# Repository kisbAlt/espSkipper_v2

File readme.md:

<div align="center">
  <picture>
    <source media="(prefers-color-scheme: dark)" srcset="./documentation/logo_dark.png">
    
  </picture>
  <h2 align="center">ESP32 Boat Instrument</h2>
</div>

## ESPSkipper

ESP32 based, open source, low cost boat instrumentation to replace proprietary marine systems.

## Features

- GPS based speed display
- Dynamic multi-function display showing real-time metrics
- Using ST7306 300x400 reflective for good outdoors visibility with custom illumination
- Multi language support
- Configuration through settings page
- Open Echo integration, supports depth readings from the TUSS4470 shield through serial connection
- Rugged 3D printed weather-resistant housing
- Reading water temp thermistors from analog transducers

## Tech Stack

**ESP32:** C++, PlatformIO, Arduino Platform, KiCad  

## Custom PCB

You can find the custom PCB files for KiCad in the hardware folder.

<div align="center" style="display: flex; justify-content: center; align-items: center; gap: 16px; flex-wrap: wrap;">

</div>

### ESP32-S3 pinout:

| Module | Signal | GPIO | Notes |
|---|---|---:|---|
| Display / LIS3DH | LCD_SCLK / SPC | GPIO12 | Shared clock for both devices |
| Display / LIS3DH | LCD_SDI / SDO / MOSI | GPIO11 | Shared data output |
| Display / LIS3DH | SDI / MISO | GPIO13 | Shared data input; ignored for LCD |
| LIS3DH | CS | GPIO10 | Dedicated chip select for device 1 |
| Display (PCB variant) | LCD_RES | GPIO4 | Alternate board mapping |
| Display (PCB variant) | LCD_D/C | GPIO9 | Alternate board mapping |
| Display (PCB variant) | LCD_CS | GPIO5 | Alternate board mapping |
| Display (PCB variant) | LCD_SCLK | GPIO12 | Alternate board mapping |
| Display (PCB variant) | LCD_SDI | GPIO11 | Alternate board mapping |
| LIS3DH (PCB variant) | SDO | GPIO13 | Alternate board mapping |
| LIS3DH (PCB variant) | SDI | GPIO11 | Alternate board mapping |
| LIS3DH (PCB variant) | SPC | GPIO12 | Alternate board mapping |
| LIS3DH (PCB variant) | CS | GPIO10 | Alternate board mapping |
| GNSS (L96-M33) | RX0 | GPIO36 | GPS receiver input |
| GNSS (L96-M33) | TX0 | GPIO37 | GPS receiver output |
| GNSS (L96-M33) | FORCE_ON | GPIO35 | Module power control |
| Serial | TX1 | GPIO6 | Serial port 1 output |
| Serial | RX1 | GPIO7 | Serial port 1 input |
| Serial | TX2 | GPIO15 | Serial port 2 output |
| Serial | RX2 | GPIO16 | Serial port 2 input |
| Buttons | BTN1 | GPIO21 | Front panel button |
| Buttons | BTN2 | GPIO14 | Front panel button |
| Buttons | BTN3 | GPIO3 | Front panel button |
| Buttons | BTN4 | GPIO8 | Front panel button |

## Instrument housing

## PCB Bill of Materials (BOM)

| Ref | Qty | Value | Notes |
|---|---:|---|---|
| U2 | 1 | ESP32-S3-WROOM-1 | Main MCU |
| U1 | 1 | L96-M33 | GNSS module |
| U4 | 1 | LIS3DH | Accelerometer |
| U5 | 1 | - | Micro USB connector |
| U6 | 1 | - | 3.3V regulator |
| BT1 | 1 | 1056 | Battery holder |
| RF1 | 1 | 6GHz | SMA antenna connector |
| FPC1 | 1 | - | Flex cable connector |
| S1, S2 | 2 | FSM8JH | Tactile switches |
| J1 | 1 | Conn_01x10_Pin | 10-pin header |
| J2, J4 | 2 | Conn_01x04_Pin | 4-pin header |
| J3 | 1 | ARDUINO_IN | Arduino interface header |
| J5, J6 | 2 | Conn_01x02_Pin | 2-pin header |
| J7 | 1 | INT1_INT2 | Interrupt header |
| D2 | 1 | SMAJ5 | TVS diode |
| D1 | 1 | - | Schottky diode |
| D6 | 1 | 3V3PWR | 3.3V power LED |
| Q1, Q2 | 2 | - | S8050 transistor pair |
| L1 | 1 | 47 nH | Inductor |
| C1, C2, C3, C4, C16, C18, C20 | 7 | 10uF | Decoupling capacitor |
| C6, C22, C23, C24, C25, C26, C27, C28, C29 | 9 | 1uF | Filter / bulk capacitor |
| C5, C7, C8, C9, C10, C11, C17, C19, C21 | 9 | 100nF | Decoupling capacitor |
| R1, R7, R8, R9, R18, R19 | 6 | 100Ω | Current / pull-up resistor |
| R10, R11, R12, R13, R16, R17 | 6 | 1kΩ | LED / logic resistor |
| R3, R4, R5, R6, R14 | 5 | 10kΩ | Pull-up / bias resistor |
| R2 | 1 | 10Ω | Series resistor |
| R15 | 1 | 0Ω | Link / jumper resistor |
| TP1 | 1 | RESET | Test point |
| TP2 | 1 | EXTINT0 | Test point |
| TP3 | 1 | JAM_DET | Test point |

## Acknowledgements

 - [Open Echo](https://github.com/Neumi/open_echo)
 - [Osptek 4.2" BWR TFT Driver for ESP32-S3 (ST7306)](https://github.com/CaiZiYuan2019/Osptek-4.2-BWR-TFT-Driver-for-ESP32-S3)

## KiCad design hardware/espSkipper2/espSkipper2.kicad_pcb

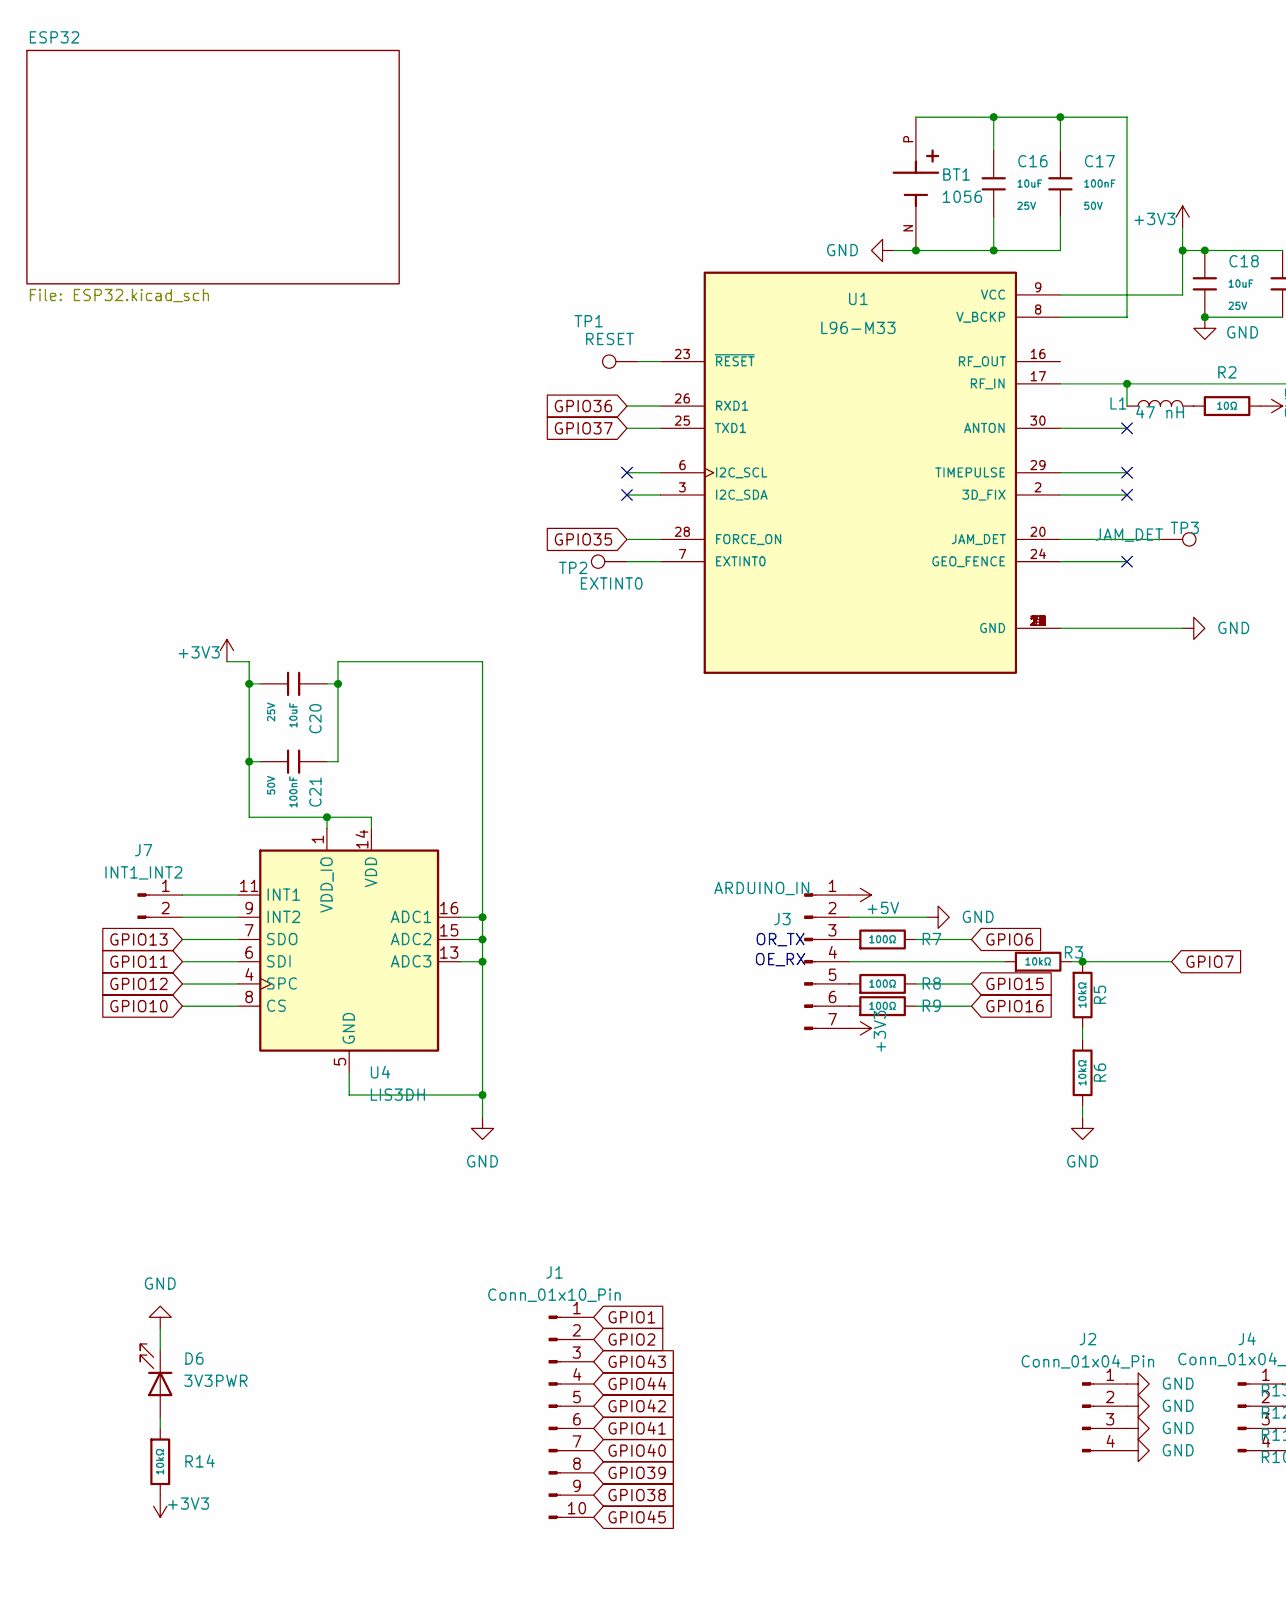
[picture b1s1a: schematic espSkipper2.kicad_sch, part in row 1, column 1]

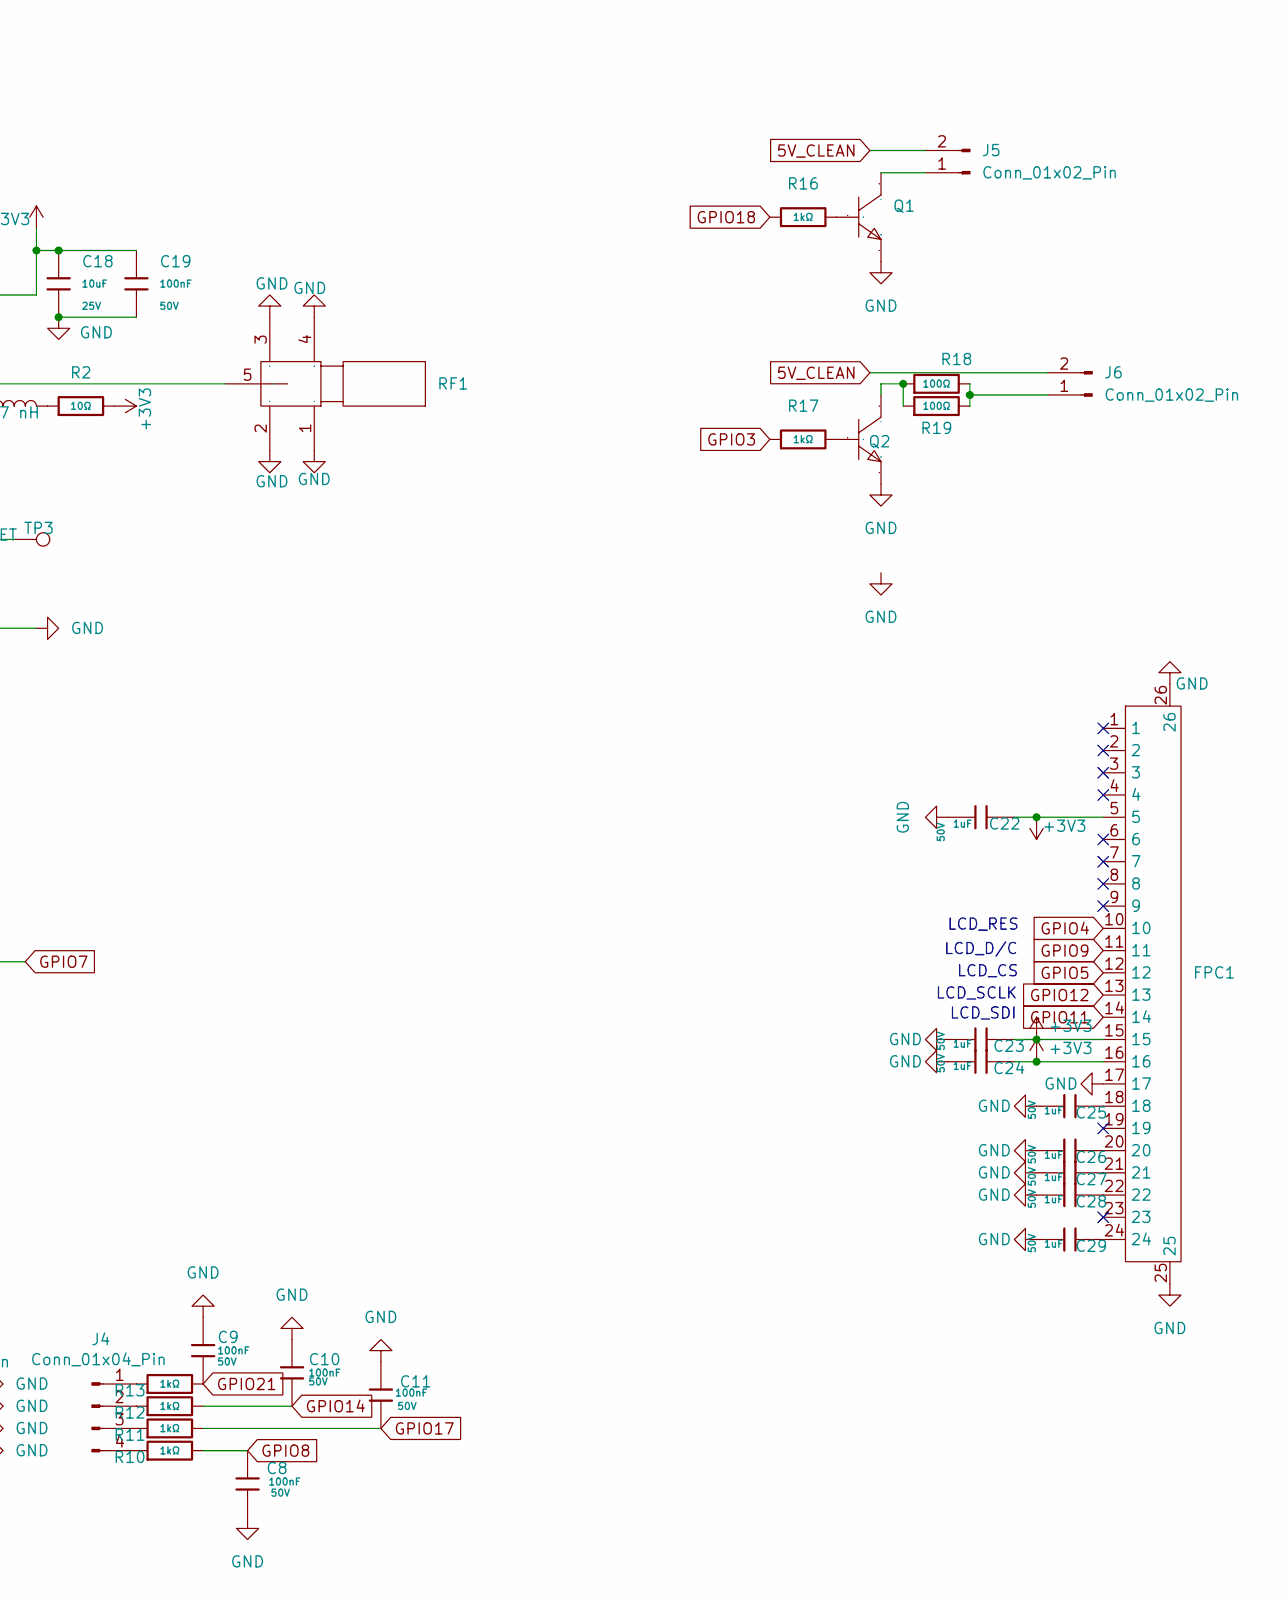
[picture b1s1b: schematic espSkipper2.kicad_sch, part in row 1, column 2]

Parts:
BT1: 1056; BAT_1056; PARTREV D
C8, C9, C10, C11, C17, C19, C21: 100nF; C_0603; Voltage Rated 50V; Tolerance ±10%; Part CC0603KRX7R9BB104; LCSC C14663
C16, C18, C20: 10uF; C_0805; Voltage Rated 25V; Tolerance ±10%; Part CL21A106KAYNNNE; LCSC C15850
C22, C23, C24, C25, C26, C27, C28, C29: 1uF; C_0805; Voltage Rated 50V; Tolerance ±10%; Part CL21B105KBFNNNE; LCSC C28323
D6: 3V3PWR; LED_D1.8mm_W3.3mm_H2.4mm
FPC1: FPC-SMD_FPC24-T1T1-2021-A; Manufacturer Part FPC24-T1T1-2021-A; LCSC Part Name 翻盖式 下接 P数:24P 间距:0.5mm
J1: Conn_01x10_Pin; PinHeader_1x10_P2.54mm_Vertical
J2, J4: Conn_01x04_Pin; PinHeader_1x04_P2.54mm_Vertical
J3: ARDUINO_IN; PinHeader_1x07_P2.54mm_Vertical
J5, J6: Conn_01x02_Pin; PinHeader_1x02_P2.54mm_Vertical
J7: INT1_INT2; PinHeader_1x02_P2.54mm_Vertical
L1: 47 nH; L_0201_0603Metric_Pad0.64x0.40mm_HandSolder
Q1, Q2: SOT-23-3_L2.9-W1.6-P1.90-LS2.8-BR; Manufacturer Part S8050; LCSC Part Name NPN 电流:500mA 电压:25V
R2: 10Ω; R_0603; Overload Voltage (Max) 75V; Tolerance ±1%; Part 0603WAF100JT5E; LCSC C22859
R3, R5, R6, R14: 10kΩ; R_0603; Overload Voltage (Max) 75V; Tolerance ±1%; Part 0603WAF1002T5E; LCSC C25804
R7, R8, R9, R18, R19: 100Ω; R_0603; Overload Voltage (Max) 75V; Tolerance ±1%; Part 0603WAF1000T5E; LCSC C22775
R10, R11, R12, R13, R16, R17: 1kΩ; R_0603; Overload Voltage (Max) 75V; Tolerance ±1%; Part 0603WAF1001T5E; LCSC C21190
RF1: 6GHz; SMA-TH_BWSMA-KE-Z001; Manufacturer Part SMA-KWE/KE-135; LCSC Part Name 内孔 SMA 正脚
TP1: RESET; PinHeader_1x01_P2.54mm_Vertical
TP2: EXTINT0; PinHeader_1x01_P2.54mm_Vertical
TP3: JAM_DET; PinHeader_1x01_P2.54mm_Vertical
U1: L96-M33; XCVR_L96-M33
U4: LIS3DH; LGA-16_3x3mm_P0.5mm_LayoutBorder3x5y

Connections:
5V_CLEAN: J5.2, J6.2; also elsewhere on the board
+3V3: C18.1, C19.1, C20.2, C21.2, C22.1, C23.1, C24.1, FPC1.5, FPC1.15, FPC1.16, J3.7, R2.2, R14.2, U1.9 (VCC), U4.1 (VDD_IO), U4.14 (VDD); also elsewhere on the board
+5V: J3.1; also elsewhere on the board
GND: BT1.N, C8.1, C9.1, C10.1, C11.1, C16.2, C17.2, C18.2, C19.2, C20.1, C21.1, C22.2, C23.2, C24.2, C25.2, C26.2, C27.2, C28.2, C29.2, D6.1 (K), FPC1.17, FPC1.25, FPC1.26, J2.1, J2.2, J2.3, J2.4, J3.2, Q1.2 (E), Q2.2 (E), R6.2, RF1.1, RF1.2, RF1.3, RF1.4, U1.4 (GND), U1.5 (GND), U1.10 (GND), U1.11 (GND), U1.12 (GND), U1.13 (GND), U1.14 (GND), U1.15 (GND), U1.18 (GND), U1.19 (GND), U1.21 (GND), U1.22 (GND), U1.27 (GND), U1.31 (GND), U4.5 (GND), U4.10 (GND), U4.12 (GND), U4.13 (ADC3), U4.15 (ADC2), U4.16 (ADC1); also elsewhere on the board
GPIO1: J1.1; also elsewhere on the board
GPIO2: J1.2; also elsewhere on the board
GPIO3: R17.1; also elsewhere on the board
GPIO4: FPC1.10; also elsewhere on the board
GPIO5: FPC1.12; also elsewhere on the board
GPIO6: R7.2; also elsewhere on the board
GPIO7: R3.2, R5.1; also elsewhere on the board
GPIO8: C8.2, R10.2; also elsewhere on the board
GPIO9: FPC1.11; also elsewhere on the board
GPIO10: U4.8 (CS); also elsewhere on the board
GPIO11: FPC1.14, U4.6 (SDI); also elsewhere on the board
GPIO12: FPC1.13, U4.4 (SPC); also elsewhere on the board
GPIO13: U4.7 (SDO); also elsewhere on the board
GPIO14: C10.2, R12.2; also elsewhere on the board
GPIO15: R8.2; also elsewhere on the board
GPIO16: R9.2; also elsewhere on the board
GPIO17: C11.2, R11.2; also elsewhere on the board
GPIO18: R16.1; also elsewhere on the board
GPIO21: C9.2, R13.2; also elsewhere on the board
GPIO35: U1.28 (FORCE_ON); also elsewhere on the board
GPIO36: U1.26 (RXD1); also elsewhere on the board
GPIO37: U1.25 (TXD1); also elsewhere on the board
GPIO38: J1.9; also elsewhere on the board
GPIO39: J1.8; also elsewhere on the board
GPIO40: J1.7; also elsewhere on the board
GPIO41: J1.6; also elsewhere on the board
GPIO42: J1.5; also elsewhere on the board
GPIO43: J1.3; also elsewhere on the board
GPIO44: J1.4; also elsewhere on the board
GPIO45: J1.10; also elsewhere on the board
unnamed: C25.1, FPC1.18
unnamed: C26.1, FPC1.20
unnamed: C27.1, FPC1.21
unnamed: C28.1, FPC1.22
unnamed: C29.1, FPC1.24
unnamed: D6.2 (A), R14.1
unnamed: J3.3, R7.1
unnamed: J3.4, R3.1
unnamed: J3.5, R8.1
unnamed: J3.6, R9.1
unnamed: J4.1, R13.1
unnamed: J4.2, R12.1
unnamed: J4.3, R11.1
unnamed: J4.4, R10.1
unnamed: J5.1, Q1.3 (C)
unnamed: J6.1, R18.2, R19.2
unnamed: J7.1, U4.11 (INT1)
unnamed: J7.2, U4.9 (INT2)
unnamed: L1.2, R2.1
unnamed: Q1.1 (B), R16.2
unnamed: Q2.1 (B), R17.2
unnamed: Q2.3 (C), R18.1, R19.1
unnamed: R5.2, R6.1
unnamed: TP2.1, U1.7 (EXTINT0)
unnamed: TP3.1, U1.20 (JAM_DET)
unnamed: L1.1, RF1.5, U1.17 (RF_IN)
unnamed: BT1.P, C16.1, C17.1, U1.8 (V_BCKP)
unnamed: TP1.1, U1.23 (~RESET)

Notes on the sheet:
LCD_RES
LCD_SCLK
OR_TX
LCD_SDI
OE_RX
LCD_D/C
LCD_CS

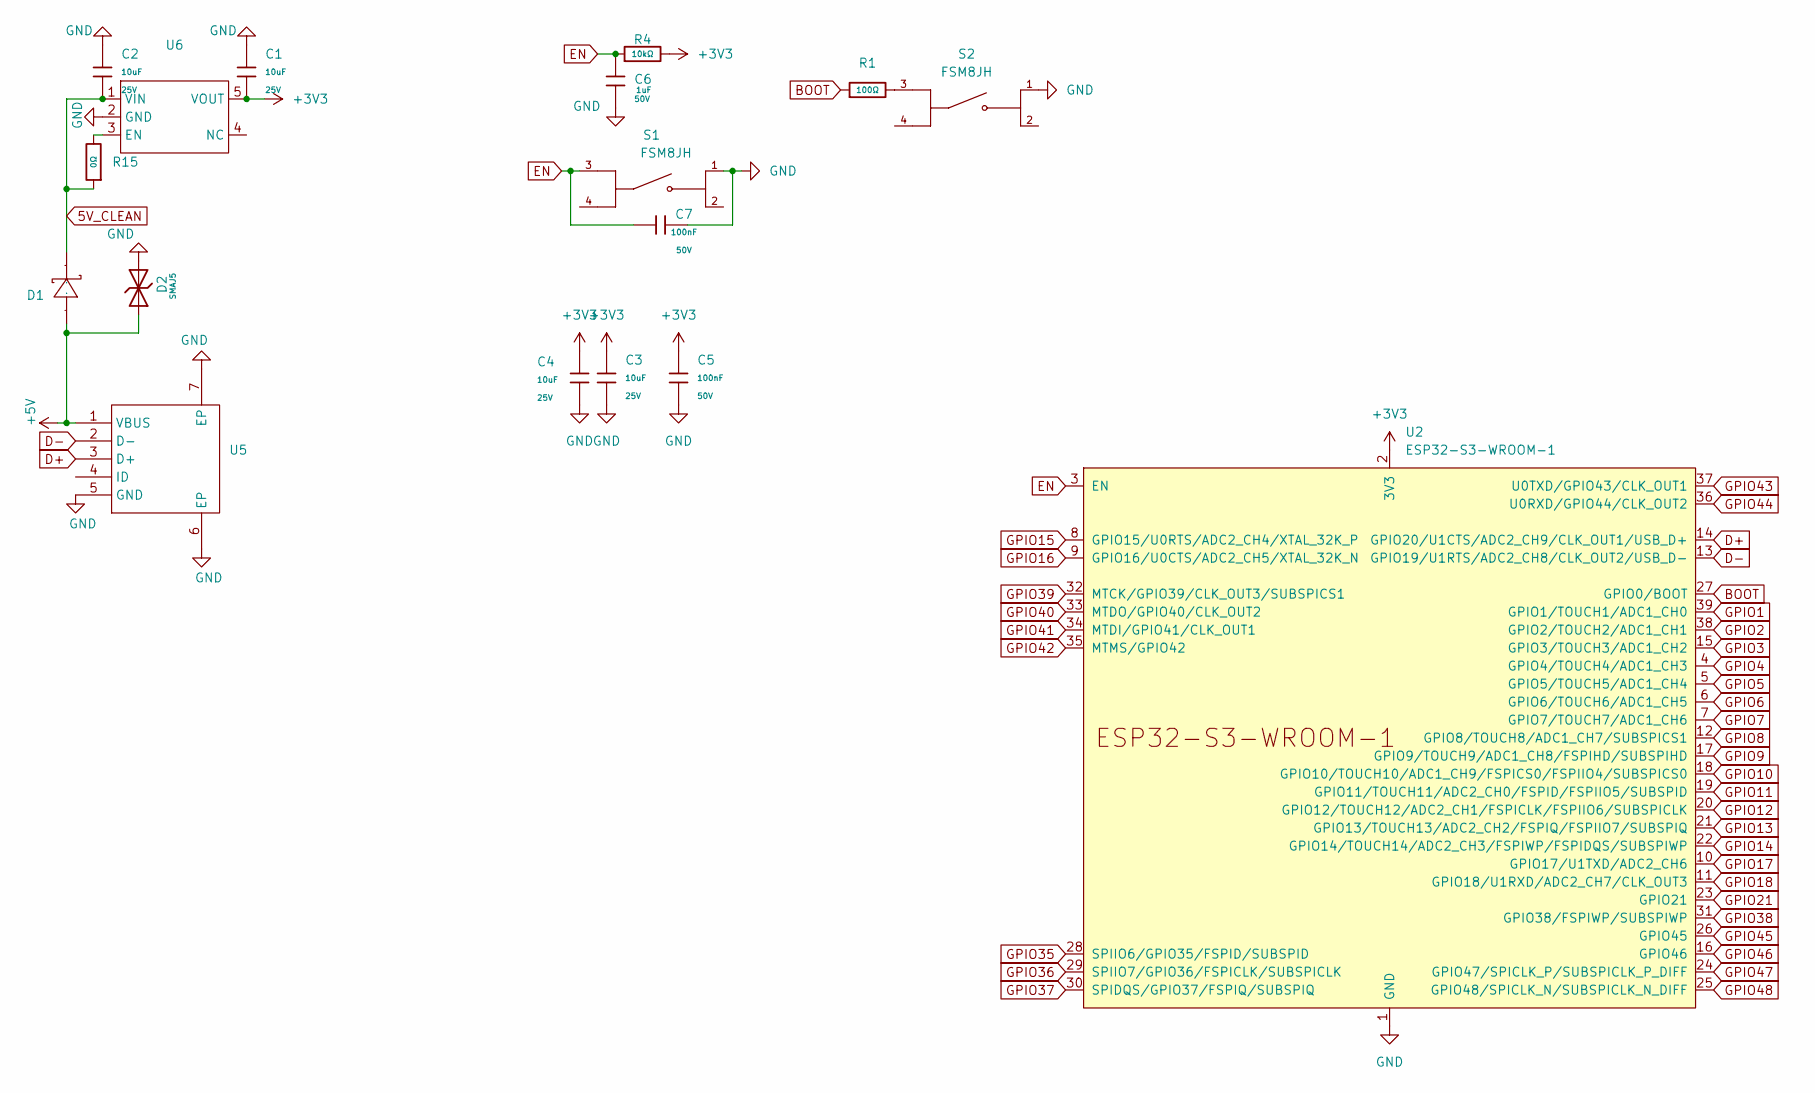
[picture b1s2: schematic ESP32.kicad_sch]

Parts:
C1, C2, C3, C4: 10uF; C_0805; Voltage Rated 25V; Tolerance ±10%; Part CL21A106KAYNNNE; LCSC C15850
C5, C7: 100nF; C_0603; Voltage Rated 50V; Tolerance ±10%; Part CC0603KRX7R9BB104; LCSC C14663
C6: 1uF; C_0805; Voltage Rated 50V; Tolerance ±10%; Part CL21B105KBFNNNE; LCSC C28323
D1: SOD-323_L1.8-W1.3-LS2.5-RD; Manufacturer Part 1N5819WS; LCSC Part Name 电压:40V 电流:1A
D2: SMAJ5; D_SMA; Part SMAJ5.0CA; LCSC C19077524
R1: 100Ω; R_0603; Overload Voltage (Max) 75V; Tolerance ±1%; Part 0603WAF1000T5E; LCSC C22775
R4: 10kΩ; R_0603; Overload Voltage (Max) 75V; Tolerance ±1%; Part 0603WAF1002T5E; LCSC C25804
R15: 0Ω; R_0603; Overload Voltage (Max) 75V; Tolerance ±1%; Part 0603WAF0000T5E; LCSC C21189
S1, S2: FSM8JH; SW_FSM8JH; PARTREV 8-1773450-9
U2: ESP32-S3-WROOM-1
U5: MICRO-USB-SMD_USB-MR-D-023; Manufacturer Part USB-MR-D-023; LCSC Part Name Micro-B 母 卧贴
U6: SOT-23-5_L2.9-W1.6-P0.95-LS2.7-BR; Manufacturer Part AP2112K-3.3TRG1(MS); LCSC Part Name AP2112K-3.3TRG1(MS)

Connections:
5V_CLEAN: C2.2, D1.1 (K), R15.1, U6.1 (VIN); also elsewhere on the board
+3V3: C1.2, C3.1, C4.1, C5.1, R4.2, U2.2 (3V3), U6.5 (VOUT); also elsewhere on the board
+5V: D1.2 (A), D2.2, U5.1 (VBUS); also elsewhere on the board
BOOT: R1.1, U2.27 (GPIO0/BOOT)
D+: U2.14 (GPIO20/U1CTS/ADC2_CH9/CLK_OUT1/USB_D+), U5.3 (D+)
D-: U2.13 (GPIO19/U1RTS/ADC2_CH8/CLK_OUT2/USB_D-), U5.2 (D-)
EN: C6.1, C7.1, R4.1, S1.3, U2.3 (EN)
GND: C1.1, C2.1, C3.2, C4.2, C5.2, C6.2, C7.2, D2.1, S1.1, S2.1, U2.1 (GND), U2.40 (GND), U2.41 (GND), U5.5 (GND), U5.6 (EP), U5.7 (EP), U6.2 (GND); also elsewhere on the board
GPIO1: U2.39 (GPIO1/TOUCH1/ADC1_CH0); also elsewhere on the board
GPIO2: U2.38 (GPIO2/TOUCH2/ADC1_CH1); also elsewhere on the board
GPIO3: U2.15 (GPIO3/TOUCH3/ADC1_CH2); also elsewhere on the board
GPIO4: U2.4 (GPIO4/TOUCH4/ADC1_CH3); also elsewhere on the board
GPIO5: U2.5 (GPIO5/TOUCH5/ADC1_CH4); also elsewhere on the board
GPIO6: U2.6 (GPIO6/TOUCH6/ADC1_CH5); also elsewhere on the board
GPIO7: U2.7 (GPIO7/TOUCH7/ADC1_CH6); also elsewhere on the board
GPIO8: U2.12 (GPIO8/TOUCH8/ADC1_CH7/SUBSPICS1); also elsewhere on the board
GPIO9: U2.17 (GPIO9/TOUCH9/ADC1_CH8/FSPIHD/SUBSPIHD); also elsewhere on the board
GPIO10: U2.18 (GPIO10/TOUCH10/ADC1_CH9/FSPICS0/FSPIIO4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); also elsewhere on the board
GPIO11: U2.19 (GPIO11/TOUCH11/ADC2_CH0/FSPID/FSPIIO5/S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); also elsewhere on the board
GPIO12: U2.20 (GPIO12/TOUCH12/ADC2_CH1/FSPICLK/FSPIIO6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); also elsewhere on the board
GPIO13: U2.21 (GPIO13/TOUCH13/ADC2_CH2/FSPIQ/FSPIIO7/S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); also elsewhere on the board
GPIO14: U2.22 (GPIO14/TOUCH14/ADC2_CH3/FSPIWP/FSPIDQS/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); also elsewhere on the board
GPIO15: U2.8 (GPIO15/U0RTS/ADC2_CH4/XTAL_32K_P); also elsewhere on the board
GPIO16: U2.9 (GPIO16/U0CTS/ADC2_CH5/XTAL_32K_N); also elsewhere on the board
GPIO17: U2.10 (GPIO17/U1TXD/ADC2_CH6); also elsewhere on the board
GPIO18: U2.11 (GPIO18/U1RXD/ADC2_CH7/CLK_OUT3); also elsewhere on the board
GPIO21: U2.23 (GPIO21); also elsewhere on the board
GPIO35: U2.28 (SPIIO6/GPIO35/FSPID/SUBSPID); also elsewhere on the board
GPIO36: U2.29 (SPIIO7/GPIO36/FSPICLK/SUBSPICLK); also elsewhere on the board
GPIO37: U2.30 (SPIDQS/GPIO37/FSPIQ/SUBSPIQ); also elsewhere on the board
GPIO38: U2.31 (GPIO38/FSPIWP/SUBSPIWP); also elsewhere on the board
GPIO39: U2.32 (MTCK/GPIO39/CLK_OUT3/SUBSPICS1); also elsewhere on the board
GPIO40: U2.33 (MTDO/GPIO40/CLK_OUT2); also elsewhere on the board
GPIO41: U2.34 (MTDI/GPIO41/CLK_OUT1); also elsewhere on the board
GPIO42: U2.35 (MTMS/GPIO42); also elsewhere on the board
GPIO43: U2.37 (U0TXD/GPIO43/CLK_OUT1); also elsewhere on the board
GPIO44: U2.36 (U0RXD/GPIO44/CLK_OUT2); also elsewhere on the board
GPIO45: U2.26 (GPIO45); also elsewhere on the board
GPIO46: U2.16 (GPIO46)
GPIO47: U2.24 (GPIO47/SPICLK_P/SUBSPICLK_P_DIFF)
GPIO48: U2.25 (GPIO48/SPICLK_N/SUBSPICLK_N_DIFF)
unnamed: R1.2, S2.3
unnamed: R15.2, U6.3 (EN)

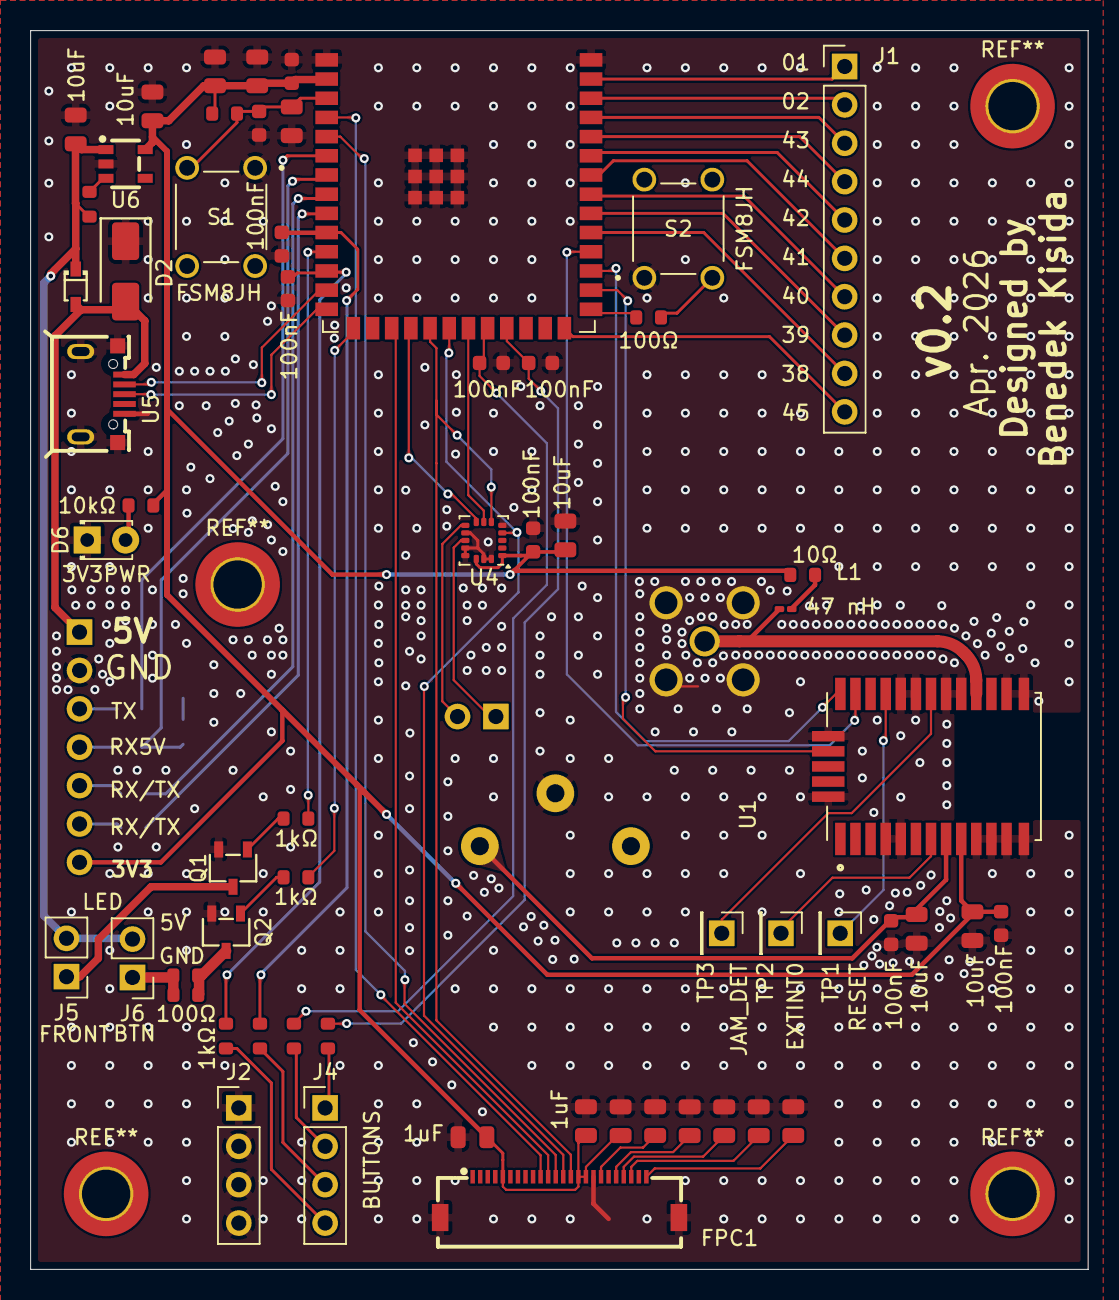
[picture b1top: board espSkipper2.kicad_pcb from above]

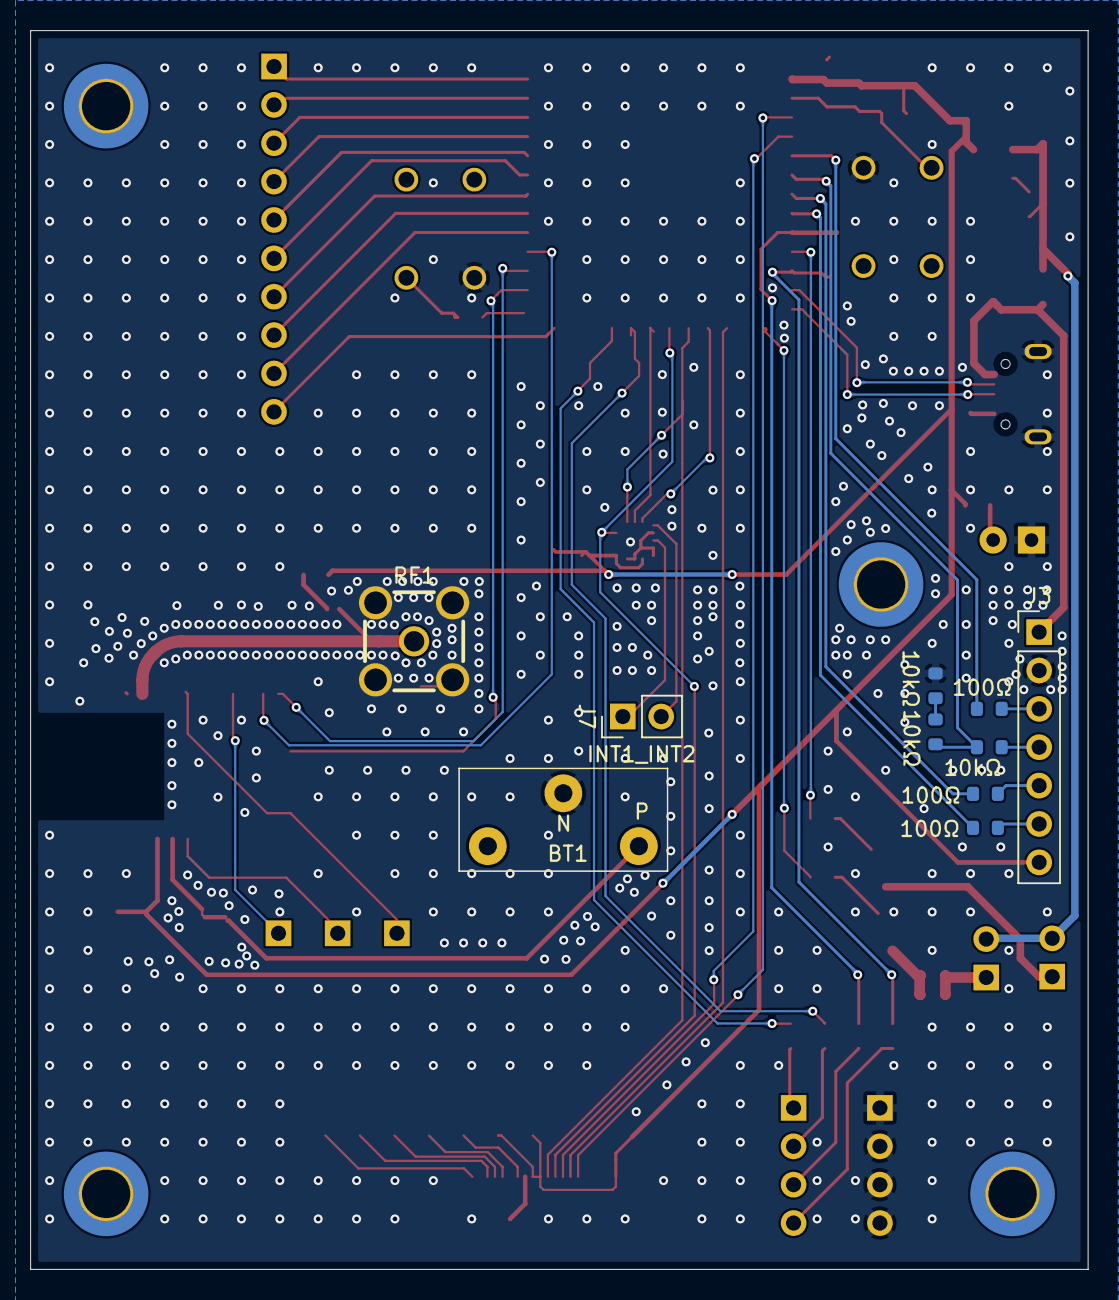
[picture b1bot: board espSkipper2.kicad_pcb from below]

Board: 2 copper layers, 70.0 x 82.0 mm, 70 parts (10 on the bottom side), 68 nets.

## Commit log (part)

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2026-06-28 initialized project with working code using all the sensors
2026-06-29 Added instrument data model logic
